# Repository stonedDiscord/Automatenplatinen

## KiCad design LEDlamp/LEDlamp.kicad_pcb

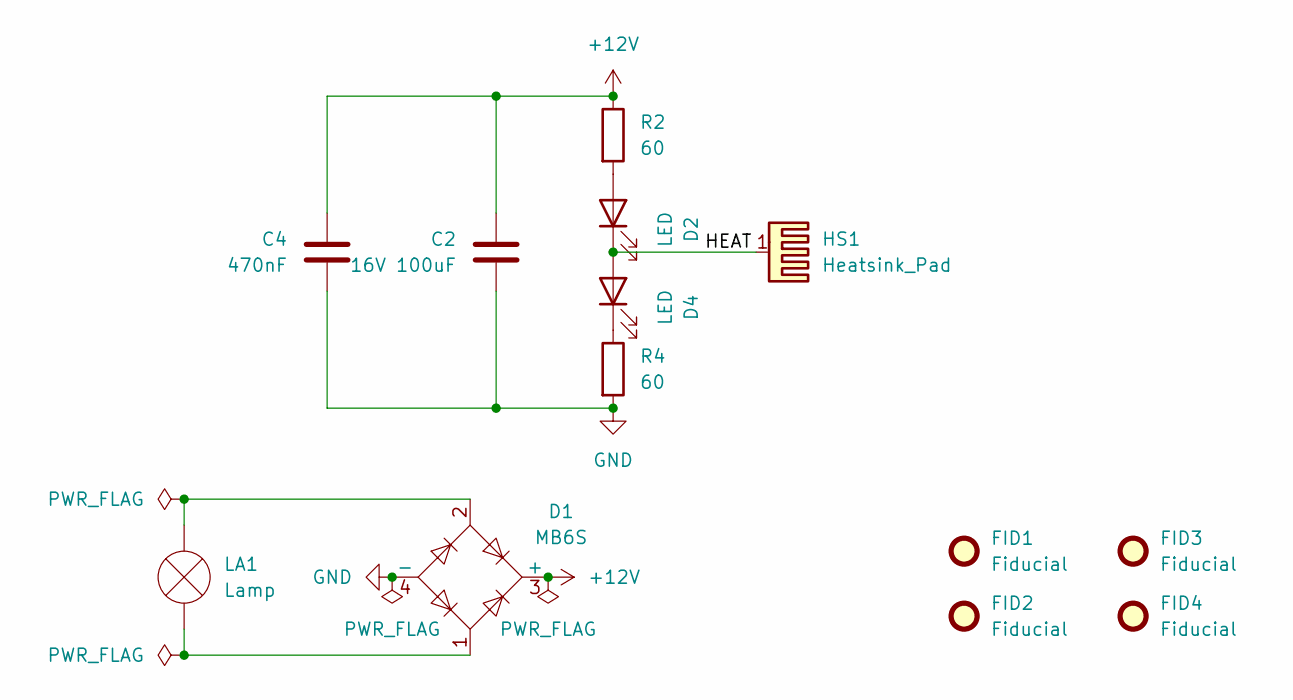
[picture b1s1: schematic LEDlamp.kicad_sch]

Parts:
C2: 16V 100uF; CP_EIA-7343-15_Kemet-W
C4: 470nF; C_0805_2012Metric_Pad1.18x1.45mm_HandSolder
D1: MB6S; TO-269AA
D2, D4: LED; LED_PLCC_2835_Handsoldering
FID1, FID3: Fiducial; Fiducial_0.5mm_Mask1mm
FID2, FID4: Fiducial; Fiducial_Cross_1.5mm_Mask2mm
HS1: Heatsink_Pad
LA1: Lamp; Lampenstecker
R2, R4: 60; R_1206_3216Metric_Pad1.30x1.75mm_HandSolder

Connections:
+12V: C2.1, C4.1, D1.3 (+), R2.1
/HEAT: D2.1 (K), D4.2 (A), HS1.1
GND: C2.2, C4.2, D1.4 (-), R4.2
unnamed: D2.2 (A), R2.2
unnamed: D4.1 (K), R4.1
unnamed: D1.2, LA1.2 (+)
unnamed: D1.1, LA1.1 (-)

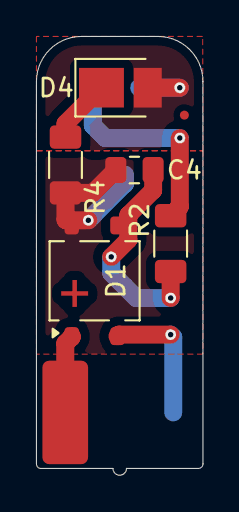
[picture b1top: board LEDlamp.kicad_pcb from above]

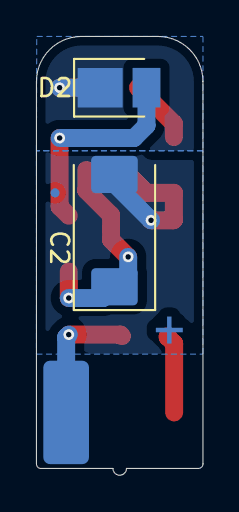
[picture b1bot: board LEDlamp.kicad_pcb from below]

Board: 2 copper layers, 9.2 x 24.4 mm, 12 parts (4 on the bottom side), 7 nets.

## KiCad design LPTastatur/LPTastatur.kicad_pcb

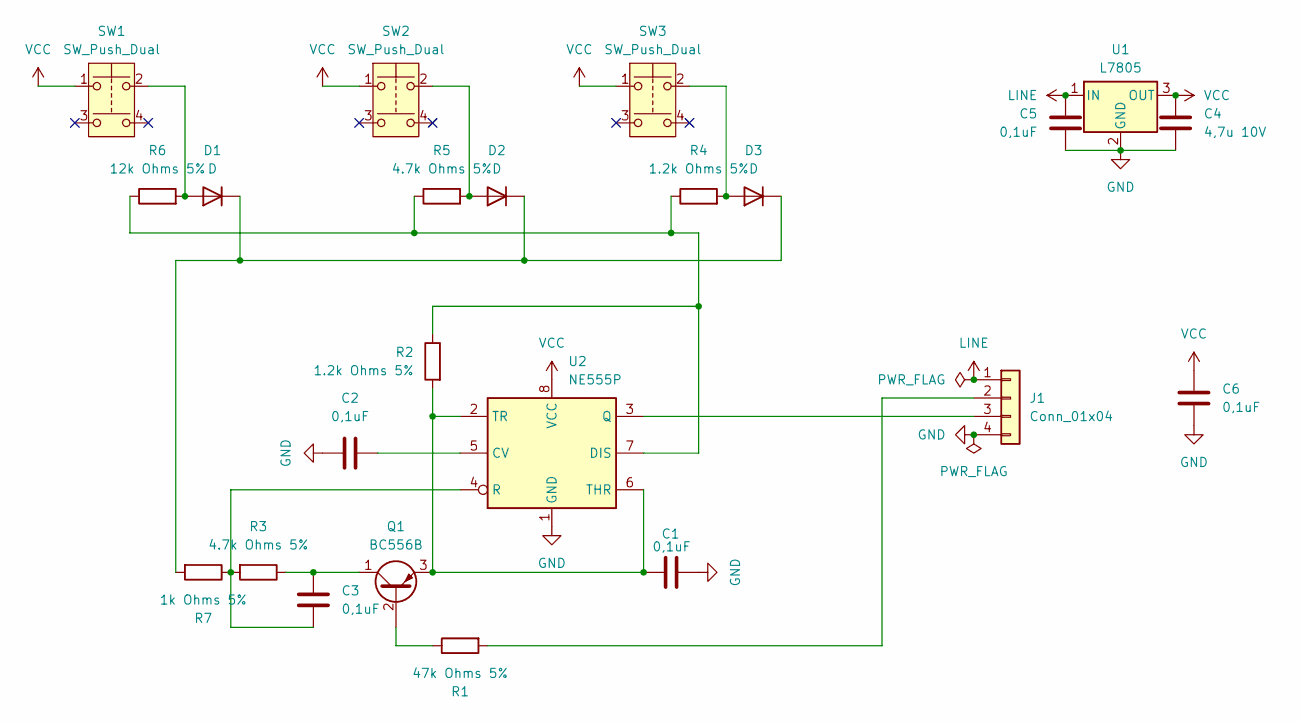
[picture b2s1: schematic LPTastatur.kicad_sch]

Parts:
C1, C2, C3, C5, C6: 0,1uF; C_Rect_L7.0mm_W2.0mm_P5.00mm
C4: 4,7u 10V; CP_Radial_Tantal_D4.5mm_P5.00mm
D1, D2, D3: D; D_A-405_P10.16mm_Horizontal
J1: Conn_01x04; PinHeader_1x04_P2.54mm_Horizontal
Q1: BC556B; TO-92L_Inline_Wide
R1: 47k Ohms 5%; R_Axial_DIN0207_L6.3mm_D2.5mm_P10.16mm_Horizontal
R2, R4: 1.2k Ohms 5%; R_Axial_DIN0207_L6.3mm_D2.5mm_P10.16mm_Horizontal
R3, R5: 4.7k Ohms 5%; R_Axial_DIN0207_L6.3mm_D2.5mm_P10.16mm_Horizontal
R6: 12k Ohms 5%; R_Axial_DIN0207_L6.3mm_D2.5mm_P10.16mm_Horizontal
R7: 1k Ohms 5%; R_Axial_DIN0207_L6.3mm_D2.5mm_P10.16mm_Horizontal
SW1, SW2, SW3: SW_Push_Dual; Push_E-Switch_KS01Q01
U1: L7805; TO-220-3_Horizontal_TabDown
U2: NE555P; DIP-8_W7.62mm

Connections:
GND: C1.1, C2.2, C4.2, C5.2, C6.1, J1.4, U1.2 (GND), U2.1 (GND)
LINE: C5.1, J1.1, U1.1 (IN)
unnamed: D1.2 (A), R6.2, SW1.2
unnamed: D1.1 (K), D2.1 (K), D3.1 (K), R7.2
unnamed: D2.2 (A), R5.2, SW2.2
unnamed: D3.2 (A), R4.2, SW3.2
unnamed: J1.2, R1.2
unnamed: J1.3, U2.3 (Q)
unnamed: Q1.2 (B), R1.1
unnamed: C3.1, Q1.1 (C), R3.1
unnamed: C1.2, Q1.3 (E), R2.2, U2.2 (TR), U2.6 (THR)
unnamed: C2.1, U2.5 (CV)
unnamed: R2.1, R4.1, R5.1, R6.1, U2.7 (DIS)
unnamed: C3.2, R3.2, R7.1, U2.4 (R)
VCC: C4.1, C6.2, SW1.1, SW2.1, SW3.1, U1.3 (OUT), U2.8 (VCC)

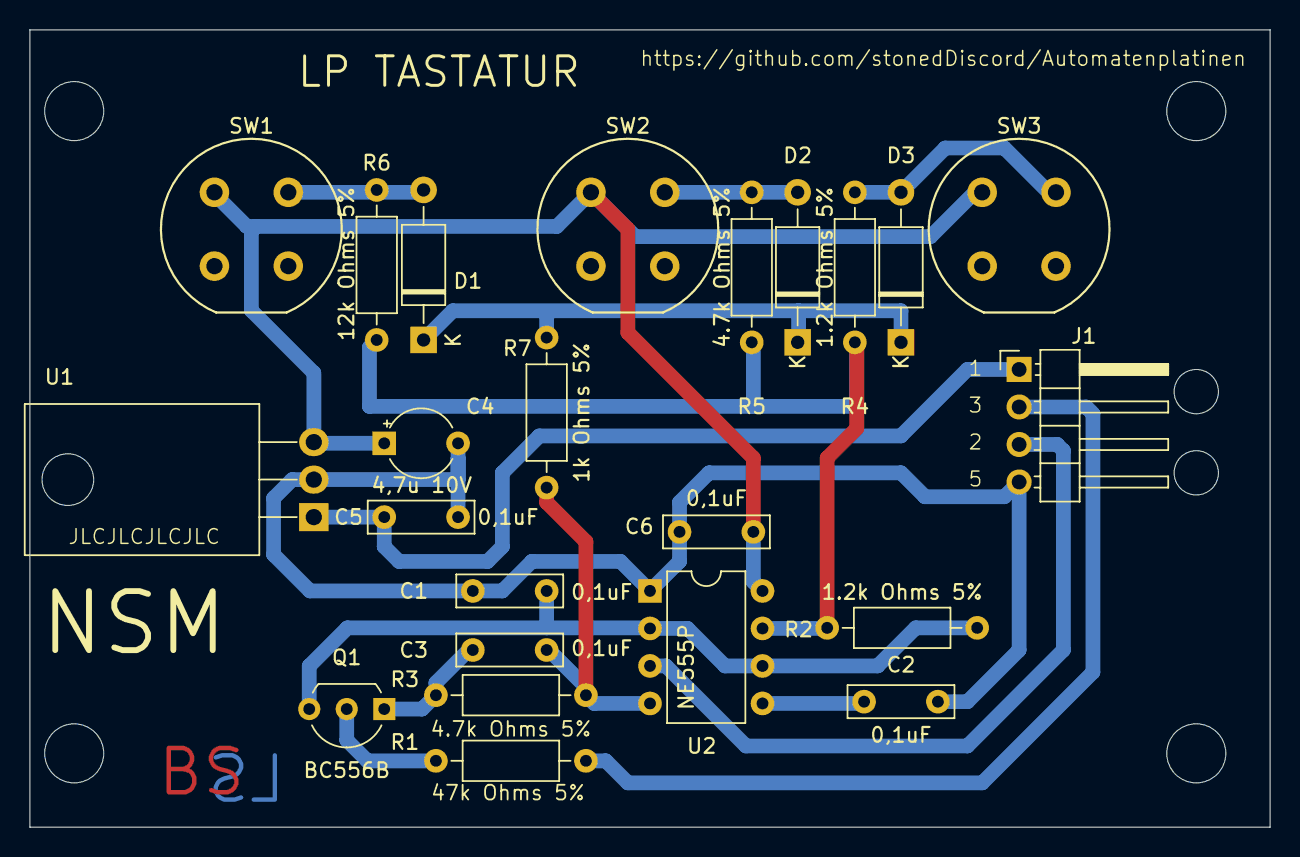
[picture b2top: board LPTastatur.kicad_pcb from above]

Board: 2 copper layers, 84.0 x 54.0 mm, 23 parts (0 on the bottom side), 15 nets.

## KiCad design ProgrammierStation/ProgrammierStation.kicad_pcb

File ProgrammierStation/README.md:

# Programmierstation

Eine Minimalversion der Steuereinheit.
Der USB-TTL ist schon integriert.

Kleiner und mehr LEDs zur Fehlersuche.

Gehäuse (passt noch nicht): RH3155

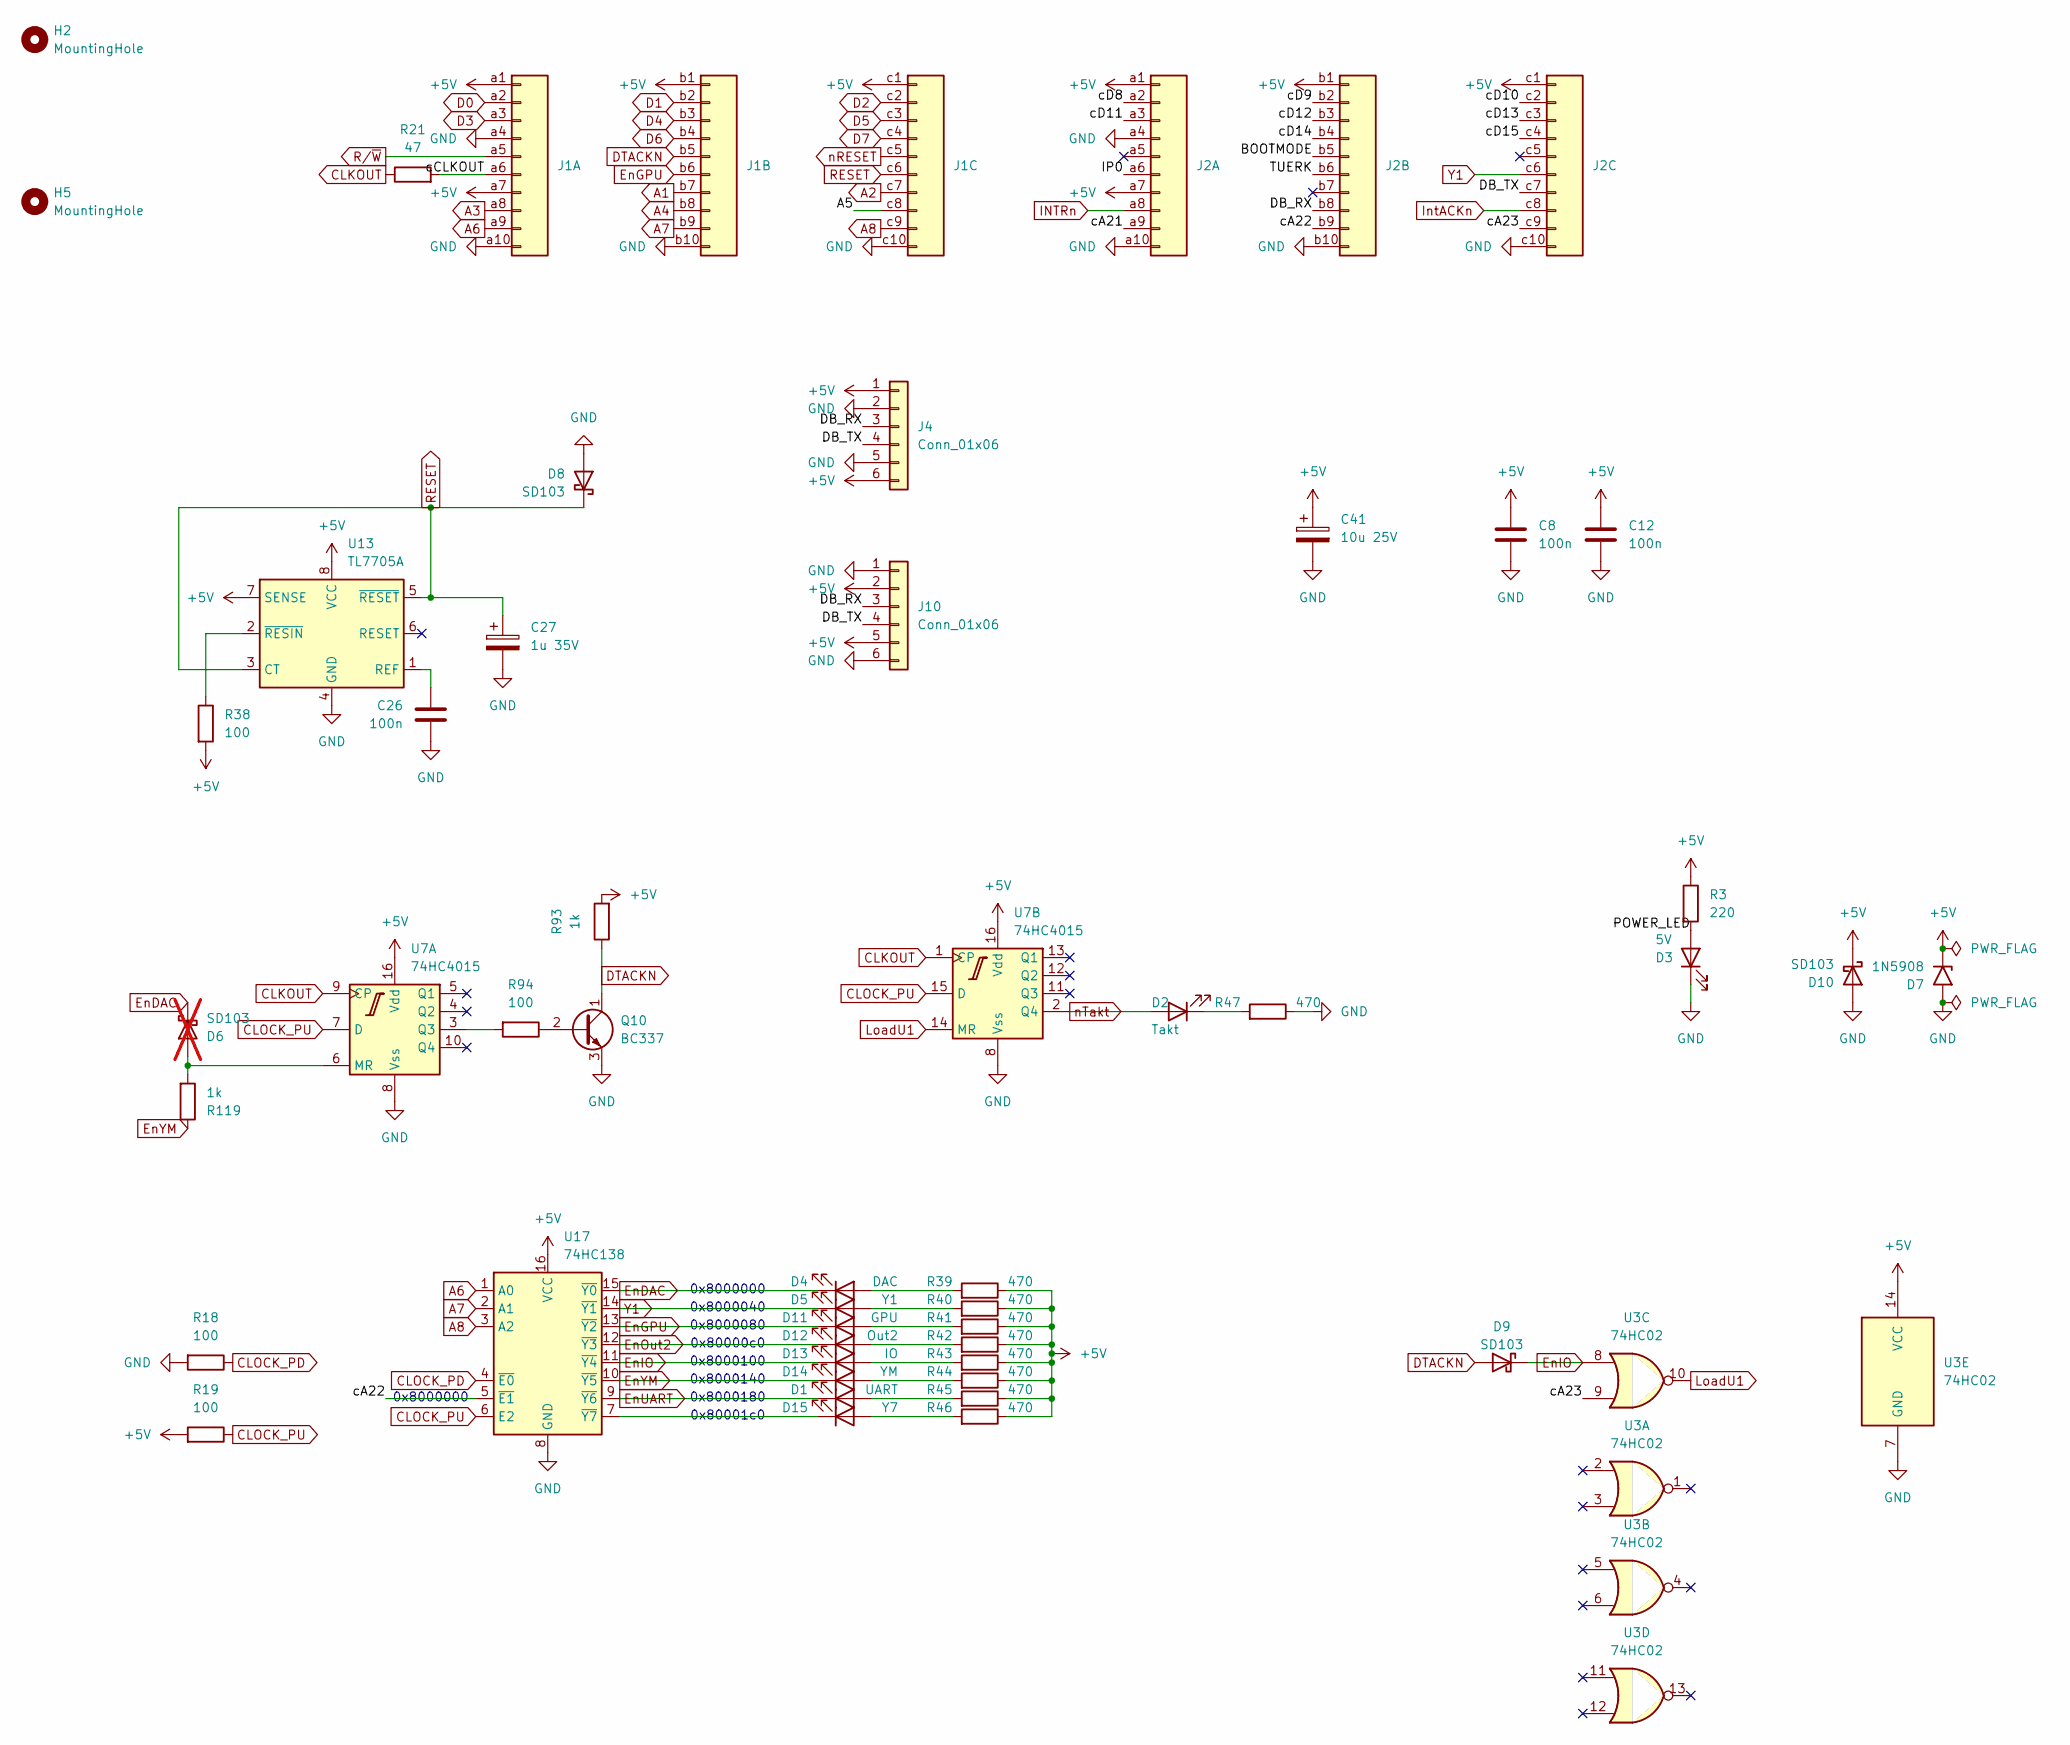
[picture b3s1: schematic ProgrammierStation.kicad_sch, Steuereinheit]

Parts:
C8, C12, C26: 100n; C_Axial_L3.8mm_D2.6mm_P7.50mm_Horizontal
C27: 1u 35V; CP_Radial_Tantal_D4.5mm_P2.50mm
C41: 10u 25V; CP_Radial_Tantal_D4.5mm_P2.50mm
D1: UART; LED_D5.0mm
D2: Takt; LED_D5.0mm
D3: 5V; LED_D5.0mm
D4: DAC; LED_D5.0mm
D5: Y1; LED_D5.0mm
D6: SD103; D_DO-35_SOD27_P7.62mm_Horizontal; not fitted
D7: 1N5908; D_DO-201AE_P15.24mm_Horizontal
D8, D9, D10: SD103; D_DO-35_SOD27_P7.62mm_Horizontal
D11: GPU; LED_D5.0mm
D12: Out2; LED_D5.0mm
D13: IO; LED_D5.0mm
D14: YM; LED_D5.0mm
D15: Y7; LED_D5.0mm
H2, H5: MountingHole; MountingHole_4.3mm_M4
J1, J2: DIN41612_03x10_ABC; DIN41612_C3_3x10_Female_Vertical_THT
J4, J10: Conn_01x06; PinHeader_1x06_P2.54mm_Vertical
Q10: BC337; TO-92
R3: 220; R_Axial_DIN0207_L6.3mm_D2.5mm_P7.62mm_Horizontal
R18, R19, R38, R94: 100; R_Axial_DIN0207_L6.3mm_D2.5mm_P7.62mm_Horizontal
R21: 47; R_Axial_DIN0207_L6.3mm_D2.5mm_P7.62mm_Horizontal
R39, R40, R41, R42, R43, R44, R45, R46, R47: 470; R_Axial_DIN0207_L6.3mm_D2.5mm_P7.62mm_Horizontal
R93, R119: 1k; R_Axial_DIN0207_L6.3mm_D2.5mm_P7.62mm_Horizontal
U3: 74HC02; DIP-14_W7.62mm
U7: 74HC4015; DIP-16_W7.62mm
U13: TL7705A; DIP-8_W7.62mm
U17: 74HC138; DIP-16_W7.62mm

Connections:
+5V: C8.1, C12.1, C41.1, D7.1 (A1), D10.1 (K), J1.a1, J1.a7, J1.b1, J1.c1, J2.a1, J2.a7, J2.b1, J2.c1, J4.1, J4.6, J10.2, J10.5, R3.1, R19.2, R38.2, R39.1, R40.1, R41.1, R42.1, R43.1, R44.1, R45.1, R46.1, R93.2, U3.14 (VCC), U7.16 (Vdd), U13.7 (SENSE), U13.8 (VCC), U17.16 (VCC)
/A5: J1.c8
/BOOTMODE: J2.b5
/DB_RX: J2.b8, J4.3, J10.3
/DB_TX: J2.c7, J4.4, J10.4
/IP0: J2.a6
/POWER_LED: D3.2 (A), R3.2
/TUERK: J2.b6
/cA21: J2.a9
/cA22: J2.b9, U17.5 (~E1)
/cA23: J2.c9, U3.9
/cCLKOUT: J1.a6, R21.2
/cD8: J2.a2
/cD9: J2.b2
/cD10: J2.c2
/cD11: J2.a3
/cD12: J2.b3
/cD13: J2.c3
/cD14: J2.b4
/cD15: J2.c4
A1: J1.b7
A2: J1.c7
A3: J1.a8
A4: J1.b8
A6: J1.a9, U17.1 (A0)
A7: J1.b9, U17.2 (A1)
A8: J1.c9, U17.3 (A2)
CLKOUT: R21.1, U7.1 (CP), U7.9 (CP)
CLOCK_PD: R18.1, U17.4 (~E0)
CLOCK_PU: R19.1, U7.7 (D), U7.15 (D), U17.6 (E2)
D0: J1.a2
D1: J1.b2
D2: J1.c2
D3: J1.a3
D4: J1.b3
D5: J1.c3
D6: J1.b4
D7: J1.c4
DTACKN: D9.2 (A), J1.b5, Q10.1 (C), R93.1
EnDAC: D4.1 (K), D6.1 (K), U17.15 (~Y0)
EnGPU: D11.1 (K), J1.b6, U17.13 (~Y2)
EnIO: D9.1 (K), D13.1 (K), U3.8, U17.11 (~Y4)
EnOut2: D12.1 (K), U17.12 (~Y3)
EnUART: D1.1 (K), U17.9 (~Y6)
EnYM: D14.1 (K), R119.1, U17.10 (~Y5)
GND: C8.2, C12.2, C26.2, C27.2, C41.2, D3.1 (K), D7.2 (A2), D8.2 (A), D10.2 (A), J1.a4, J1.a10, J1.b10, J1.c10, J2.a4, J2.a10, J2.b10, J2.c10, J4.2, J4.5, J10.1, J10.6, Q10.3 (E), R18.2, R47.1, U3.7 (GND), U7.8 (Vss), U13.4 (GND), U17.8 (GND)
INTRn: J2.a8
IntACKn: J2.c8
LoadU1: U3.10, U7.14 (MR)
unnamed: D1.2 (A), R45.2
unnamed: D2.1 (K), R47.2
unnamed: D4.2 (A), R39.2
unnamed: D5.2 (A), R40.2
unnamed: D6.2 (A), R119.2, U7.6 (MR)
unnamed: D11.2 (A), R41.2
unnamed: D12.2 (A), R42.2
unnamed: D13.2 (A), R43.2
unnamed: D14.2 (A), R44.2
unnamed: D15.2 (A), R46.2
unnamed: D15.1 (K), U17.7 (~Y7)
unnamed: Q10.2 (B), R94.1
unnamed: R94.2, U7.3 (Q3)
unnamed: C26.1, U13.1 (REF)
unnamed: R38.1, U13.2 (~RESIN)
RESET: C27.1, D8.1 (K), J1.c6, U13.3 (CT), U13.5 (~RESET)
R/~W: J1.a5
Y1: D5.1 (K), J2.c6, U17.14 (~Y1)
nRESET: J1.c5
nTakt: D2.2 (A), U7.2 (Q4)

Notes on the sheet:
0x8000100
0x8000180
0x8000000
0x8000080
0x80001c0
0x8000140
0x8000040
0x80000c0

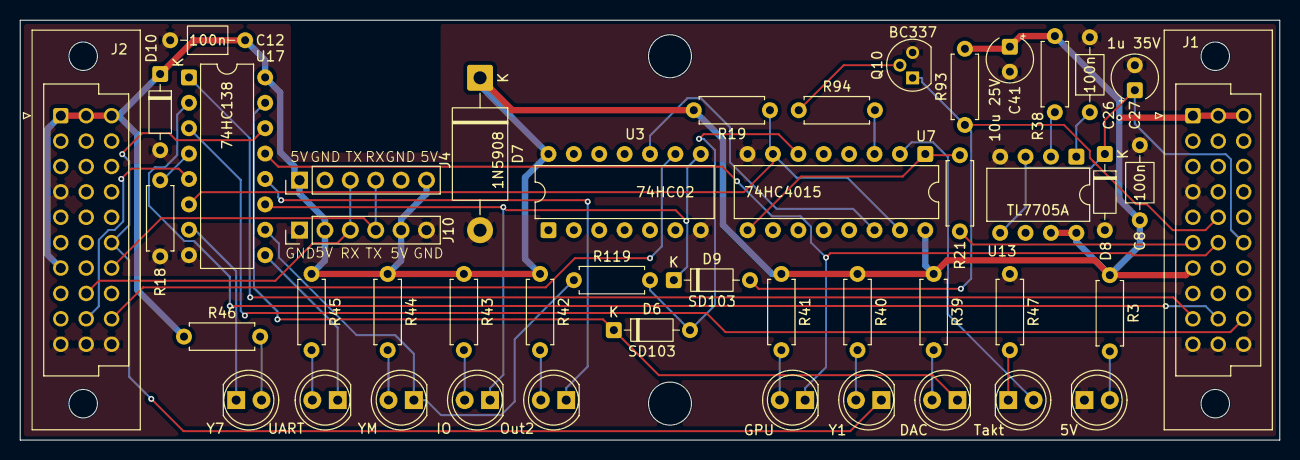
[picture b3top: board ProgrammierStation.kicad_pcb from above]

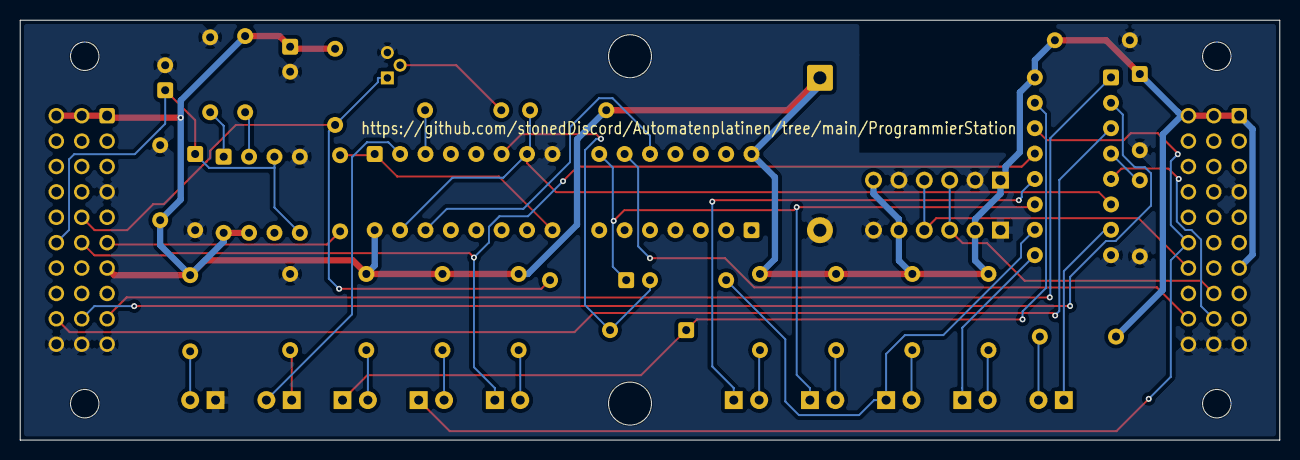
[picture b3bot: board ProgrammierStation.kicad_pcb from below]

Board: 2 copper layers, 126.0 x 42.0 mm, 48 parts (2 on the bottom side), 40 nets.

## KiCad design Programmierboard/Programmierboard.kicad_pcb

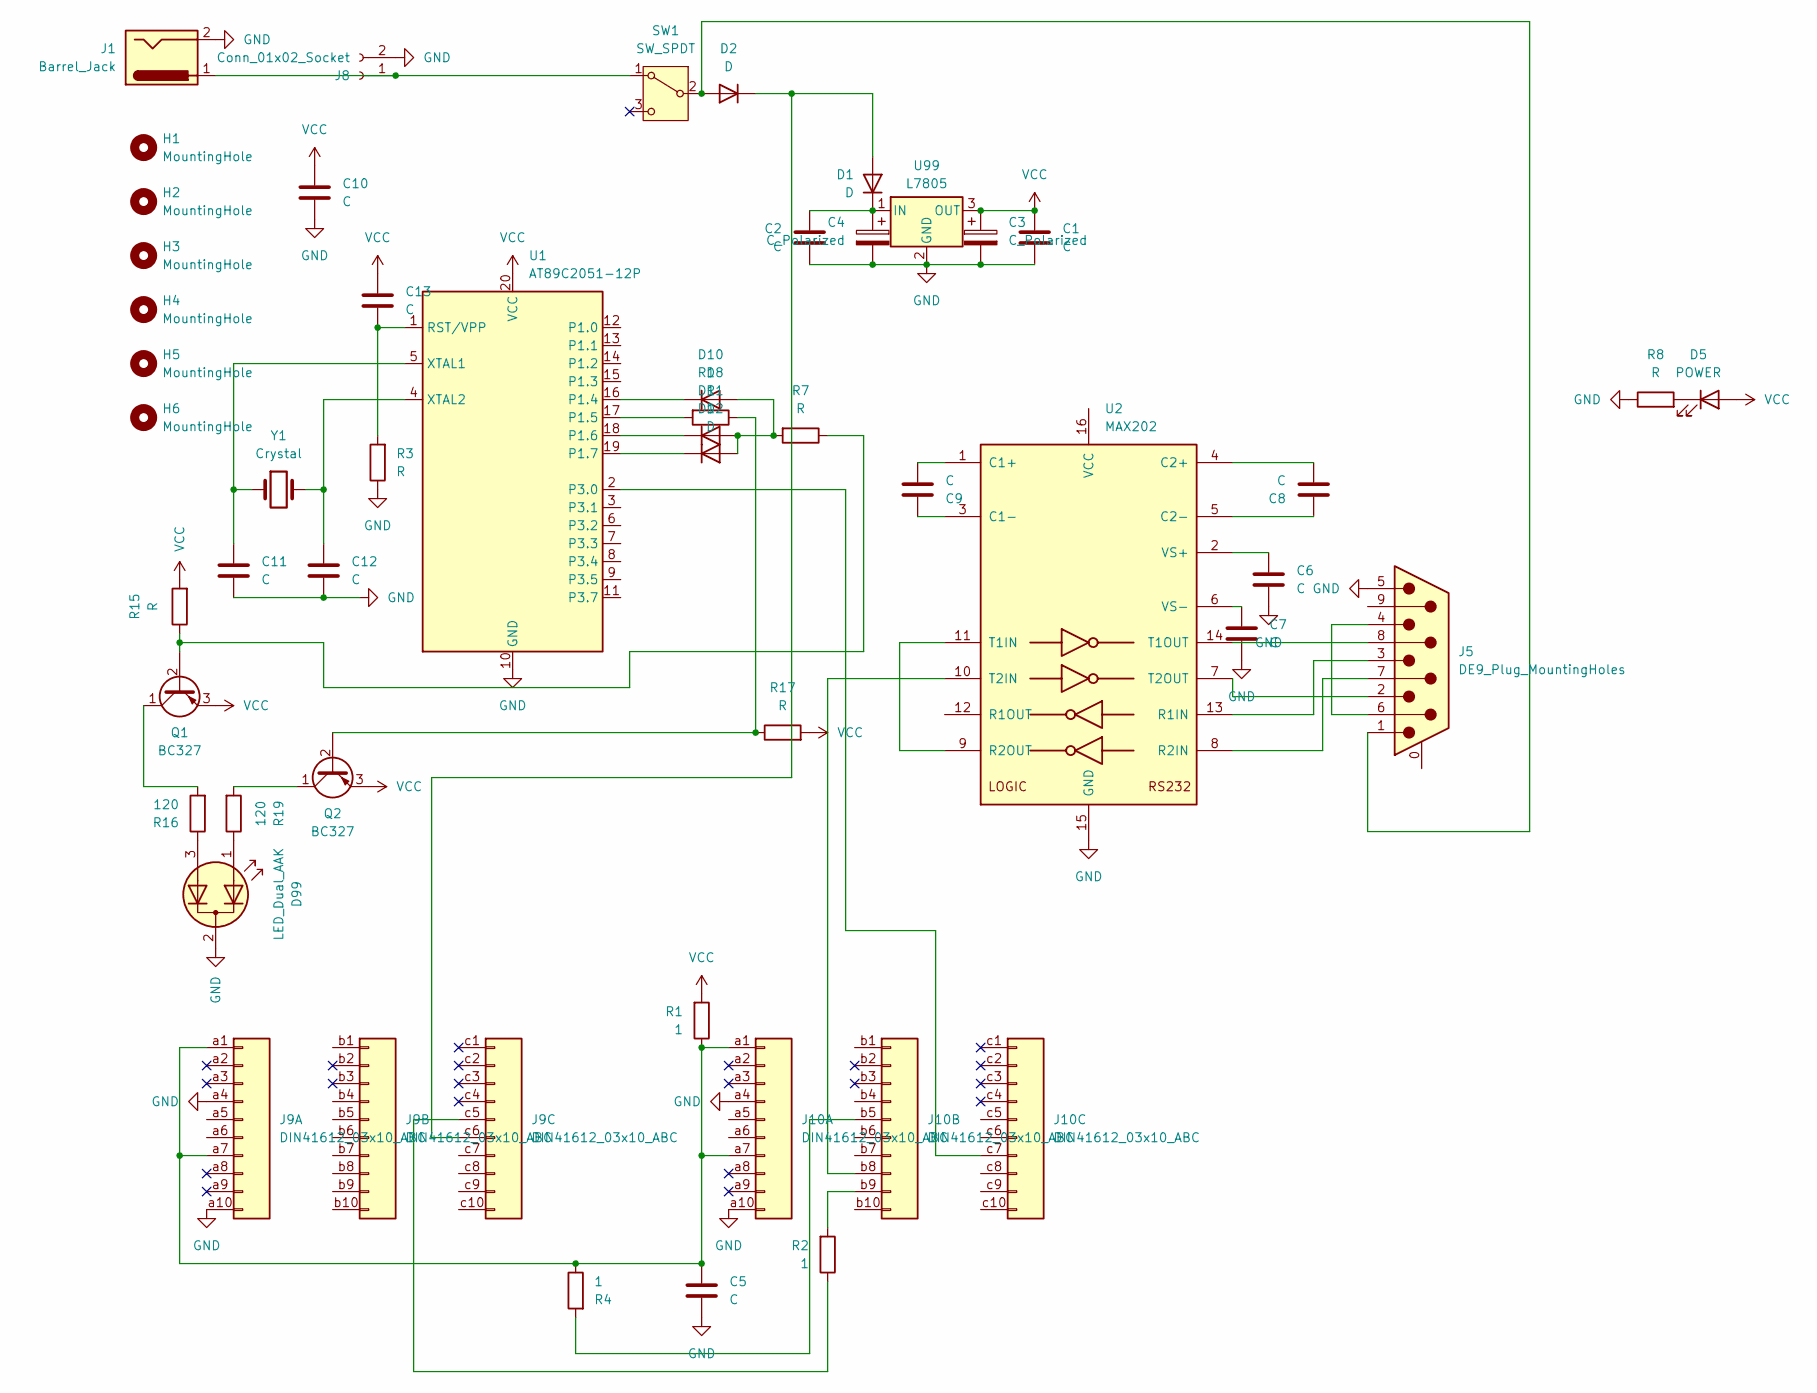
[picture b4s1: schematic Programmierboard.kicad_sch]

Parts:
C1, C2, C5, C6, C7, C8, C9, C10: C; C_Axial_L3.8mm_D2.6mm_P7.50mm_Horizontal
C3, C4: C_Polarized; CP_Axial_L21.0mm_D8.0mm_P28.00mm_Horizontal
C11, C12: C; C_Disc_D4.3mm_W1.9mm_P5.00mm
C13: C; CP_Radial_Tantal_D4.5mm_P2.50mm
D1, D2: D; D_DO-15_P15.24mm_Horizontal
D5: POWER; LED_D5.0mm
D10, D11, D12: D; D_A-405_P10.16mm_Horizontal
D99: LED_Dual_AAK; LED_D5.0mm-3
H1, H2, H3, H4, H5, H6: MountingHole; MountingHole_3.2mm_M3_DIN965
J1: Barrel_Jack; BarrelJack_SwitchcraftConxall_RAPC10U_Horizontal
J5: DE9_Plug_MountingHoles; DSUB-9_Socket_Horizontal_P2.77x2.84mm_EdgePinOffset7.70mm_H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
J8: Conn_01x02_Socket; PinSocket_1x02_P2.54mm_Vertical
J9, J10: DIN41612_03x10_ABC; DIN41612_C3_3x10_Female_Vertical_THT
Q1, Q2: BC327; TO-92
R1, R2, R4: 1; R_Axial_DIN0207_L6.3mm_D2.5mm_P10.16mm_Horizontal
R3, R7, R8, R15, R17, R18: R; R_Axial_DIN0207_L6.3mm_D2.5mm_P10.16mm_Horizontal
R16, R19: 120; R_Axial_DIN0207_L6.3mm_D2.5mm_P10.16mm_Horizontal
SW1: SW_SPDT; SW_E-Switch_EG1224_SPDT_Angled
U1: AT89C2051-12P; DIP-20_W7.62mm
U2: MAX202; DIP-16_W7.62mm
U99: L7805; TO-220-3_Horizontal_TabDown
Y1: Crystal; Crystal_HC18-U_Vertical

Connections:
GND: C1.2, C2.2, C3.2, C4.2, C5.2, C6.2, C7.2, C10.2, C11.2, C12.2, D99.2 (K), J1.2, J5.5, J8.2, J9.a4, J9.a10, J10.a4, J10.a10, R3.1, R8.1, U1.10 (GND), U2.15 (GND), U99.2 (GND)
unnamed: D1.2 (A), D2.1 (K), J9.c6
unnamed: C2.1, C4.1, D1.1 (K), U99.1 (IN)
unnamed: D2.2 (A), J5.1, SW1.2 (B)
unnamed: D5.1 (K), R8.2
unnamed: D10.2 (A), D11.2 (A), D12.2 (A), R7.2
unnamed: D10.1 (K), U1.16 (P1.4)
unnamed: D11.1 (K), U1.18 (P1.6)
unnamed: D12.1 (K), U1.19 (P1.7)
unnamed: D99.1 (A1), R19.1
unnamed: D99.3 (A2), R16.1
unnamed: J5.4, J5.6
unnamed: J1.1, J8.1, SW1.1 (A)
unnamed: J9.c5, R2.1
unnamed: C5.1, J9.a1, J9.a7, J10.a1, J10.a7, R1.1, R4.1
unnamed: J10.b5, R4.2
unnamed: J10.b8, U2.10 (T2IN)
unnamed: J10.b9, R2.2
unnamed: J10.c7, U1.2 (P3.0)
unnamed: Q1.2 (B), R7.1, R15.1
unnamed: Q1.1 (C), R16.2
unnamed: Q2.2 (B), R17.1, R18.1
unnamed: Q2.1 (C), R19.2
unnamed: R18.2, U1.17 (P1.5)
unnamed: C13.2, R3.2, U1.1 (RST/VPP)
unnamed: C11.1, U1.5 (XTAL1), Y1.1
unnamed: C12.1, U1.4 (XTAL2), Y1.2
unnamed: C9.2, U2.1 (C1+)
unnamed: C9.1, U2.3 (C1-)
unnamed: C8.2, U2.4 (C2+)
unnamed: C8.1, U2.5 (C2-)
unnamed: J5.3, U2.13 (R1IN)
unnamed: J5.7, U2.8 (R2IN)
unnamed: U2.9 (R2OUT), U2.11 (T1IN)
unnamed: J5.8, U2.14 (T1OUT)
unnamed: J5.2, U2.7 (T2OUT)
unnamed: C6.1, U2.2 (VS+)
unnamed: C7.1, U2.6 (VS-)
VCC: C1.1, C3.1, C10.1, C13.1, D5.2 (A), Q1.3 (E), Q2.3 (E), R1.2, R15.2, R17.2, U1.20 (VCC), U99.3 (OUT)

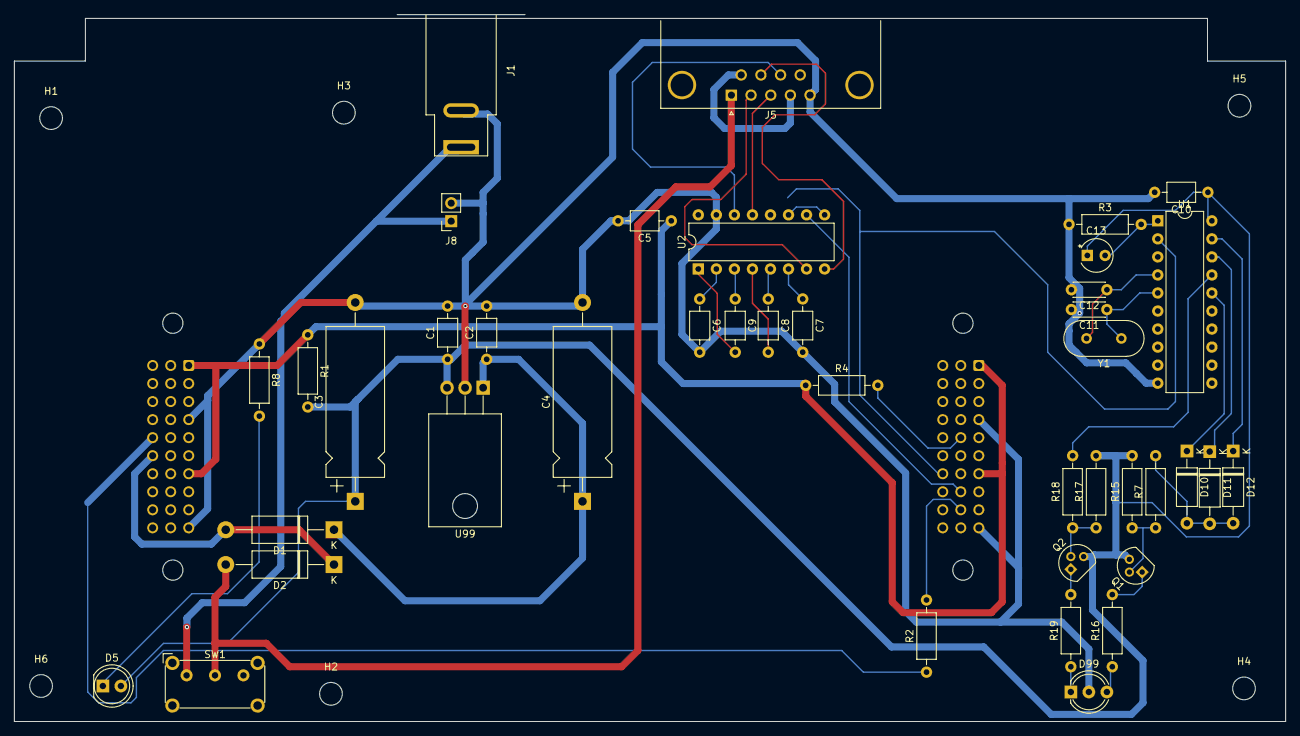
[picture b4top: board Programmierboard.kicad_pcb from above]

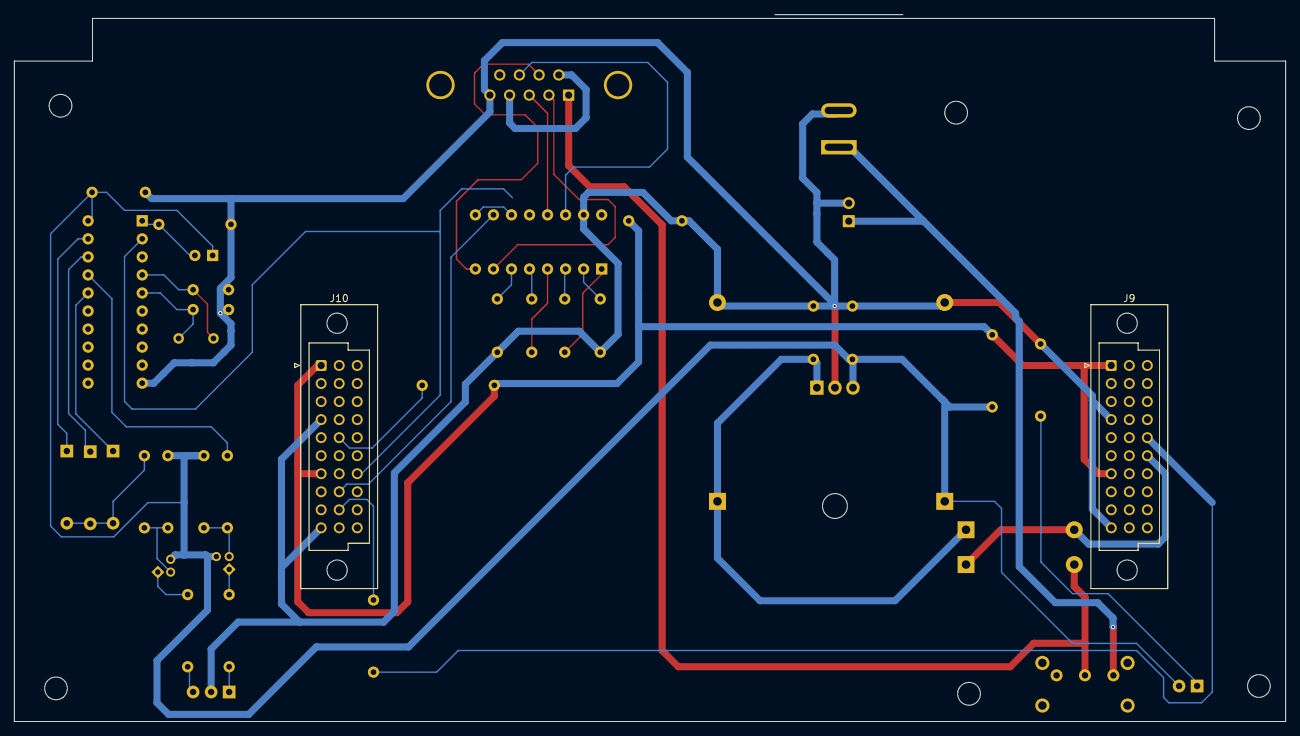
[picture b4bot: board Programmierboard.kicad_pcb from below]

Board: 2 copper layers, 179.0 x 99.5 mm, 49 parts (2 on the bottom side), 39 nets.

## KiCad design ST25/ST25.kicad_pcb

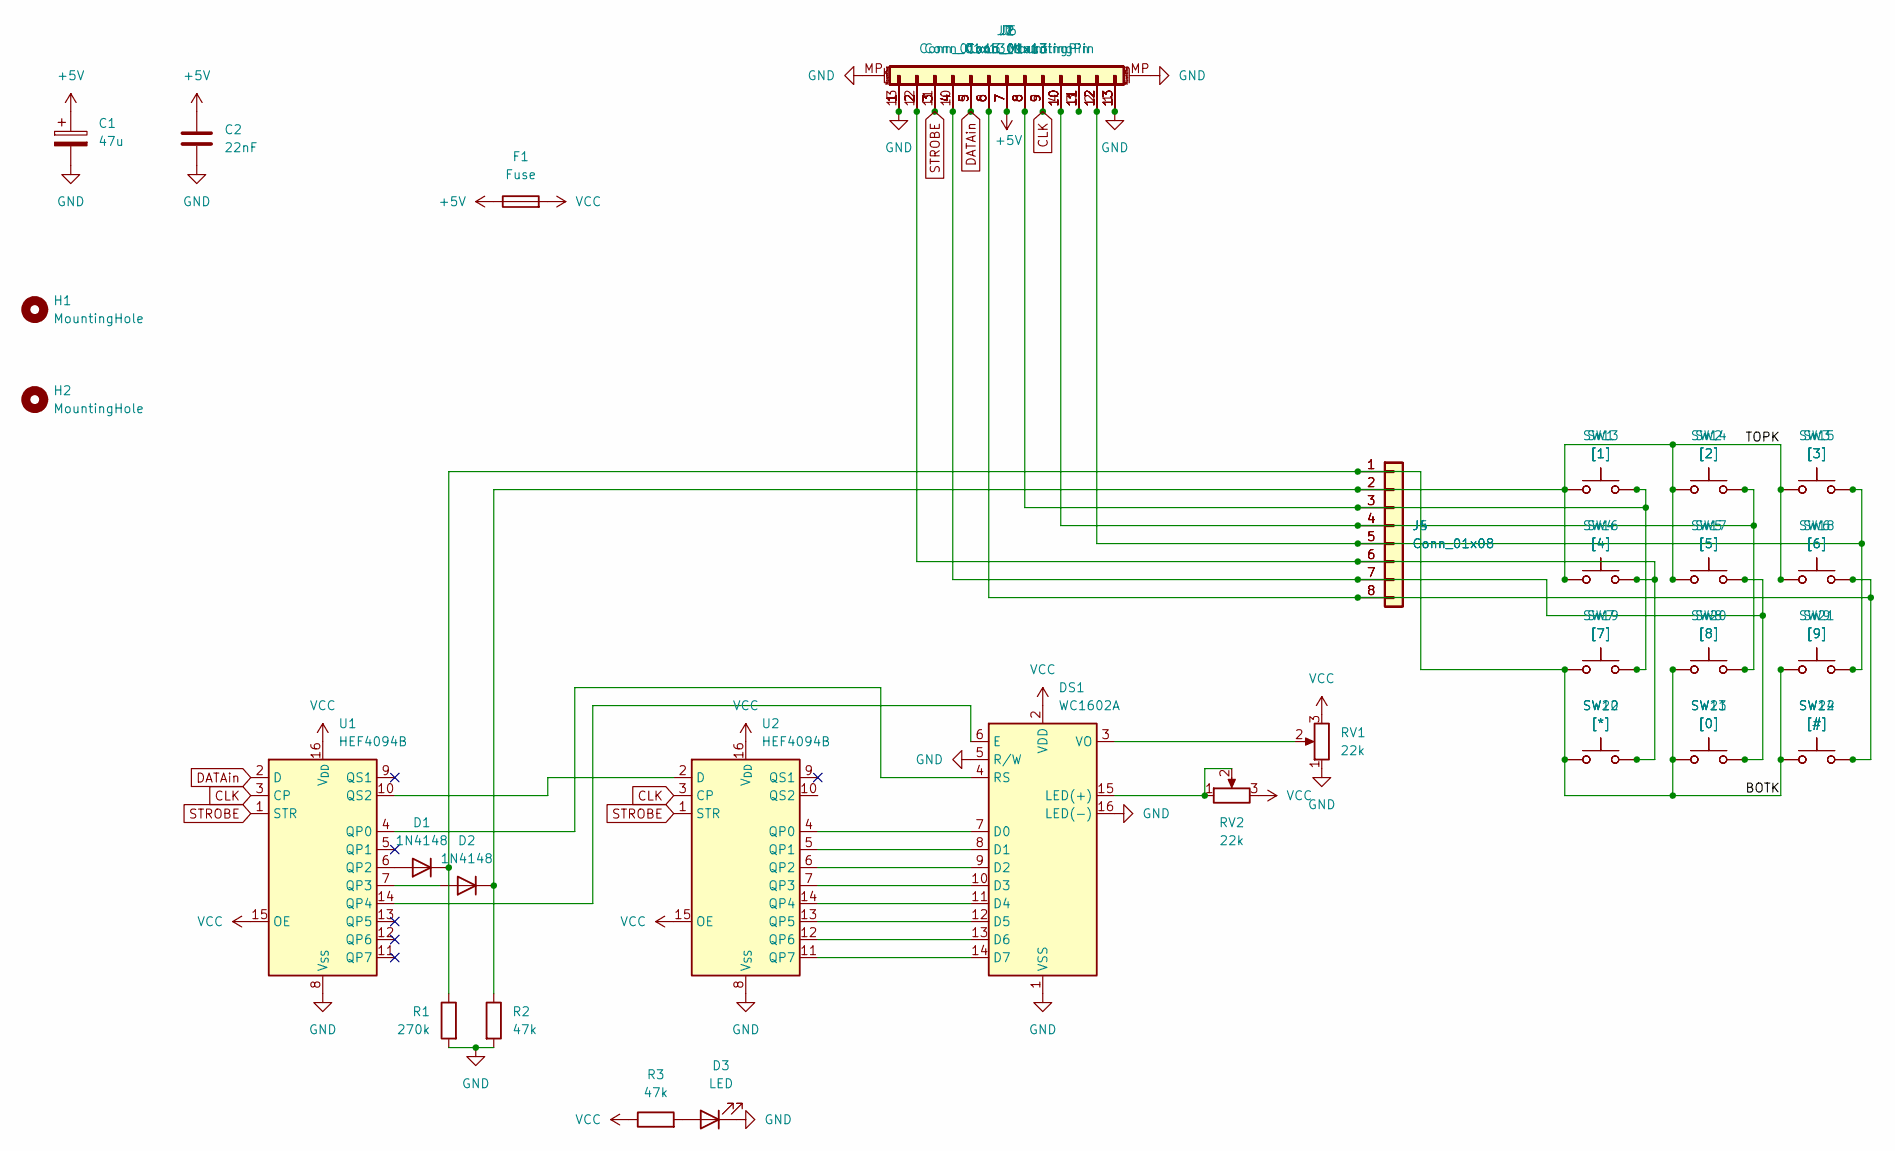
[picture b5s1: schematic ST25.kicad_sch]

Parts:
C1: 47u; CP_EIA-7360-38_Kemet-E
C2: 22nF; C_0603_1608Metric
D1, D2: 1N4148; D_DO-35_SOD27_P7.62mm_Horizontal
D3: LED; LED_0603_1608Metric
DS1: WC1602A
F1: Fuse; Fuse_0603_1608Metric
H1, H2: MountingHole; MountingHole_3mm
J1: Conn_01x13; Service
J2: Conn_01x13; PinHeader_1x13_P2.54mm_Vertical
J4, J5: Conn_01x08; PinHeader_1x08_P2.54mm_Vertical
J6: Conn_01x13_MountingPin; TE_1-84952-3_1x13-1MP_P1.0mm_Horizontal
J7: Conn_01x13_MountingPin; TE_1-84953-3_1x13-1MP_P1.0mm_Horizontal
R1: 270k; R_0603_1608Metric
R2, R3: 47k; R_0603_1608Metric
RV1, RV2: 22k; Potentiometer_ACP_CA9-V10_Vertical_Hole
SW1: [1]; SW_PUSH_6mm
SW2: [2]; SW_PUSH_6mm
SW3: [3]; SW_PUSH_6mm
SW4: [4]; SW_PUSH_6mm
SW5: [5]; SW_PUSH_6mm
SW6: [6]; SW_PUSH_6mm
SW7: [7]; SW_PUSH_6mm
SW8: [8]; SW_PUSH_6mm
SW9: [9]; SW_PUSH_6mm
SW10: [*]; SW_PUSH_6mm
SW11: [0]; SW_PUSH_6mm
SW12: [#]; SW_PUSH_6mm
SW13: [1]; SW_SPST_Omron_B3F-40xx
SW14: [2]; SW_SPST_Omron_B3F-40xx
SW15: [3]; SW_SPST_Omron_B3F-40xx
SW16: [4]; SW_SPST_Omron_B3F-40xx
SW17: [5]; SW_SPST_Omron_B3F-40xx
SW18: [6]; SW_SPST_Omron_B3F-40xx
SW19: [7]; SW_SPST_Omron_B3F-40xx
SW20: [8]; SW_SPST_Omron_B3F-40xx
SW21: [9]; SW_SPST_Omron_B3F-40xx
SW22: [*]; SW_SPST_Omron_B3F-40xx
SW23: [0]; SW_SPST_Omron_B3F-40xx
SW24: [#]; SW_SPST_Omron_B3F-40xx
U1, U2: HEF4094B; SOIC-16W_5.3x10.2mm_P1.27mm

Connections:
+5V: C1.1, C2.1, F1.1, J1.7, J2.7, J6.7, J7.7
/BOTK: D1.1 (K), J4.1, J5.1, R1.1, SW7.1, SW8.1, SW9.1, SW10.1, SW11.1, SW12.1, SW19.1, SW20.1, SW21.1, SW22.1, SW23.1, SW24.1
/TOPK: D2.1 (K), J4.2, J5.2, R2.1, SW1.1, SW2.1, SW3.1, SW4.1, SW5.1, SW6.1, SW13.1, SW14.1, SW15.1, SW16.1, SW17.1, SW18.1
CLK: J1.9, J2.9, J6.9, J7.5, U1.3 (CP), U2.3 (CP)
DATAin: J1.5, J2.5, J6.5, J7.9, U1.2 (D)
GND: C1.2, C2.2, D3.1 (K), DS1.1 (VSS), DS1.5 (R/W), DS1.16 (LED(-)), J1.1, J1.13, J2.1, J2.13, J6.1, J6.13, J6.MP (MountPin), J7.1, J7.13, J7.MP (MountPin), R1.2, R2.2, RV1.1, U1.8 (V_{SS}), U2.8 (V_{SS})
unnamed: D1.2 (A), U1.6 (QP2)
unnamed: D2.2 (A), U1.7 (QP3)
unnamed: D3.2 (A), R3.2
unnamed: DS1.7 (D0), U2.4 (QP0)
unnamed: DS1.8 (D1), U2.5 (QP1)
unnamed: DS1.9 (D2), U2.6 (QP2)
unnamed: DS1.10 (D3), U2.7 (QP3)
unnamed: DS1.11 (D4), U2.14 (QP4)
unnamed: DS1.12 (D5), U2.13 (QP5)
unnamed: DS1.13 (D6), U2.12 (QP6)
unnamed: DS1.14 (D7), U2.11 (QP7)
unnamed: DS1.6 (E), U1.14 (QP4)
unnamed: DS1.15 (LED(+)), RV2.1, RV2.2
unnamed: DS1.4 (RS), U1.4 (QP0)
unnamed: DS1.3 (VO), RV1.2
unnamed: J1.2, J2.2, J4.6, J5.6, J6.2, J7.12, SW4.2, SW10.2, SW16.2, SW22.2
unnamed: J1.4, J2.4, J4.7, J5.7, J6.4, J7.10, SW5.2, SW11.2, SW17.2, SW23.2
unnamed: J1.6, J2.6, J4.8, J5.8, J6.6, J7.8, SW6.2, SW12.2, SW18.2, SW24.2
unnamed: J1.8, J2.8, J4.3, J5.3, J6.8, J7.6, SW1.2, SW7.2, SW13.2, SW19.2
unnamed: J1.10, J2.10, J4.4, J5.4, J6.10, J7.4, SW2.2, SW8.2, SW14.2, SW20.2
unnamed: J1.11, J2.11, J6.11, J7.3
unnamed: J1.12, J2.12, J4.5, J5.5, J6.12, J7.2, SW3.2, SW9.2, SW15.2, SW21.2
unnamed: U1.10 (QS2), U2.2 (D)
STROBE: J1.3, J2.3, J6.3, J7.11, U1.1 (STR), U2.1 (STR)
VCC: DS1.2 (VDD), F1.2, R3.1, RV1.3, RV2.3, U1.15 (OE), U1.16 (V_{DD}), U2.15 (OE), U2.16 (V_{DD})

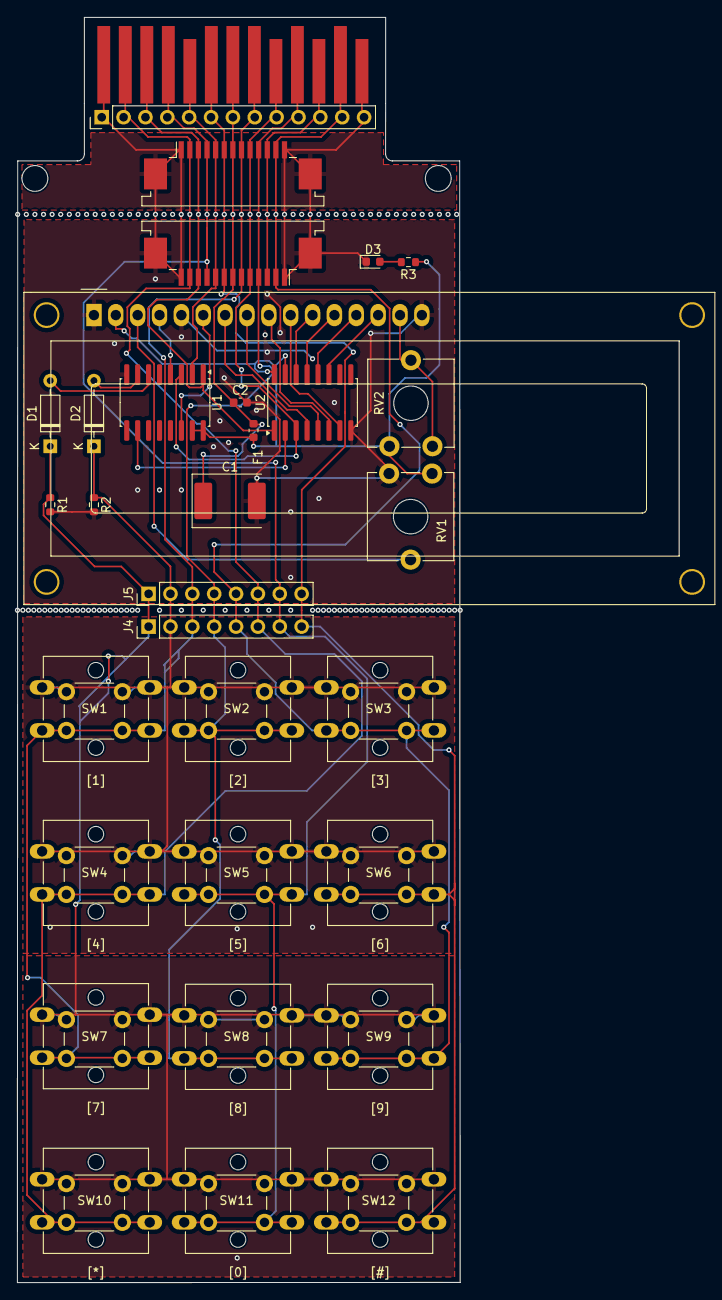
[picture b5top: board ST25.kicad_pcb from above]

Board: 2 copper layers, 51.4 x 147.0 mm, 46 parts (0 on the bottom side), 31 nets.
